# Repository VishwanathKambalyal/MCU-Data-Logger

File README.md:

# 📌 MCU Data Logger

## 📖 Overview

MCU Data Logger is a **hardware-based data logging system** designed to record and store data efficiently. The system is built using the **ATmega328P-AU microcontroller**, **24LC1025 EEPROM**, and **DS1337 RTC** for precise timekeeping. The hardware is designed in **KiCad 9**, with **2-layer PCB**.

### 🔹 Key Components

- **🖥️ ATmega328P-AU (MCU)**
  - Serves as the main processing unit.
  - Handles data acquisition, processing, and communication.
  - Supports multiple communication protocols (UART, SPI, I2C).

- **💾 24LC1025 EEPROM (I2C Storage)**
  - Provides non-volatile memory for data storage.
  - Communicates via the I2C protocol.
  - Can store up to **1 Mbit** of data.

- **⏳ DS1337 Real-Time Clock (RTC)**
  - Maintains accurate timestamps for logged data.
  - Operates using the I2C protocol.
  - Supports alarms and timekeeping even in power-off conditions.

- **🔌 Power System**
  - Operates on a **5V** power supply.
  - Includes **ground (GND) connections** for circuit stability.

- **📡 Communication Interfaces**
  - **UART (Tx, Rx)** for serial communication.
  - **SPI (SCK, MOSI, MISO, RESET)** for high-speed data transfer.
  - **I2C (SDA, SCL)** for sensor and memory communication.

- **🖲️ General-Purpose Input/Output (GPIO)**
  - Available on **D2-D8** pins.
  - Can be used for external sensors or control signals.

---

## 🔧 Features

- ✅ **Microcontroller**: ATmega328P-AU
- ✅ **Memory Storage**: 24LC1025 EEPROM (I2C)
- ✅ **Real-Time Clock (RTC)**: DS1337 (I2C)
- ✅ **Interfaces**:
  - **UART**: Tx, Rx
  - **SPI**: SCK, MOSI, MISO, RESET
  - **I2C**: SDA, SCL
- ✅ **Power Supply**: 5V
- ✅ **GPIOs**: D2-D8 for peripheral connections

---

## 📷 Project Images

### 🔹 Schematic Diagram

### 🔹 PCB Designs

### 🔹 3D PCB Views

| Top View                             | Bottom View                          |
| ------------------------------------ | ------------------------------------ |
|        |   |

---

## 🔌 How to Use

### 1️⃣ Clone the Repository
```bash
git clone https://github.com/VishwanathKambalyal/MCU-Data-Logger.git
```
### 2️⃣ Open Hardware Files in KiCad 9
Navigate to the Hardware folder.
Open the schematic (.sch) and PCB (.kicad_pcb) files.

### 3️⃣ Customize & Manufacture
Modify the PCB design if required.
Generate Gerber files for PCB fabrication.

## 📜 License
This project is licensed under the MIT License – you are free to use, modify, and distribute it as needed.

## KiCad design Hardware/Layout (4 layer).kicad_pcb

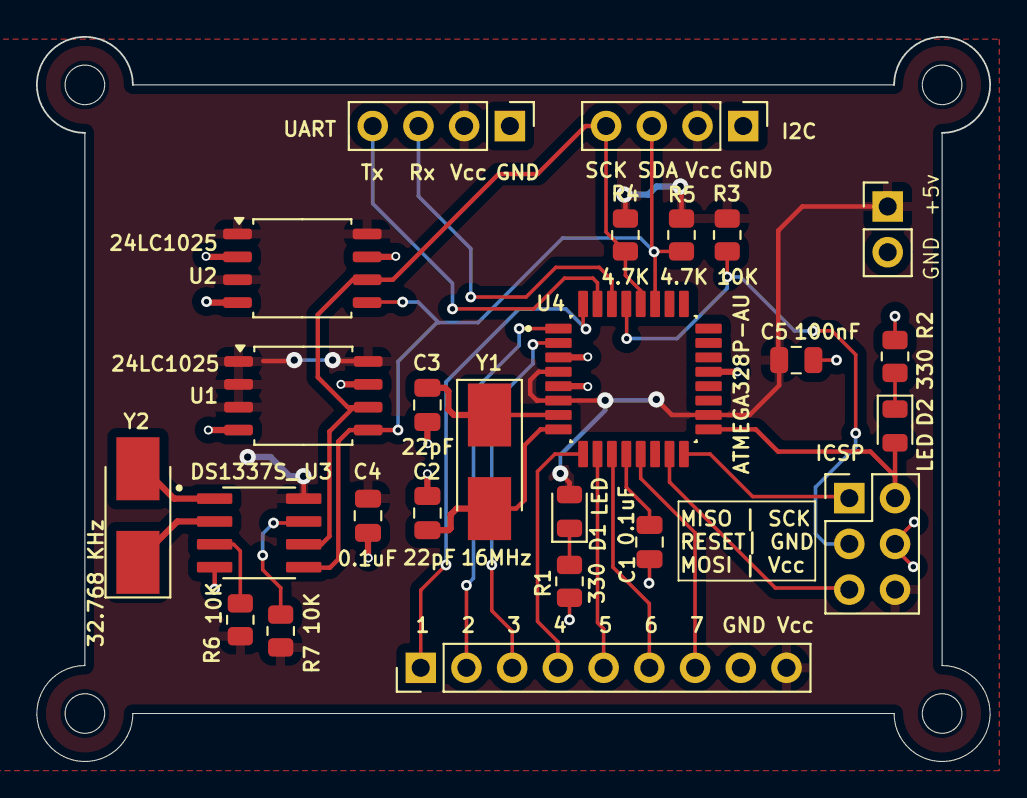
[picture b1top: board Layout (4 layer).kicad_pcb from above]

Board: 2 copper layers, 53.0 x 40.2 mm, 29 parts (0 on the bottom side), 26 nets.

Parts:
BT1: Battery_Cell; PinHeader_1x02_P2.54mm_Vertical
C1, C4: 0.1uF; C_0805_2012Metric
C2, C3: 22pF; C_0805_2012Metric
C5: 100nF; C_0805_2012Metric
D1, D2: LED; LED_0805_2012Metric
H1, H2, H3, H4: MountingHole; MountingHole_2.2mm_M2
J1, J2: Conn_01x04_Pin; PinHeader_1x04_P2.54mm_Vertical
J3: Conn_01x09_Pin; PinHeader_1x09_P2.54mm_Vertical
J4: Conn_02x03_Counter_Clockwise; PinHeader_2x03_P2.54mm_Vertical
R1, R2: 330; R_0805_2012Metric
R3, R6, R7: 10K; R_0805_2012Metric
R4, R5: 4.7K; R_0805_2012Metric
U1, U2: 24LC1025; SOIC-8_5.23x5.23mm_P1.27mm
U3: DS1337S_; SOIC127P600X175-8N
U4: ATMEGA328P-AU; QFP80P900X900X120-32N
Y1: 16MHz; Crystal_SMD_5032-2Pin_5.0x3.2mm_HandSoldering
Y2: 32.768 KHz; Crystal_SMD_5032-2Pin_5.0x3.2mm_HandSoldering

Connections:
/D2: J3.1, U4.32 (PD2)
/D3: J3.2, U4.1 (PD3)
/D4: J3.3, U4.2 (PD4)
/D5: J3.4, U4.9 (PD5)
/D6: J3.5, U4.10 (PD6)
/D7: J3.6, U4.11 (PD7)
/D8: J3.7, U4.13 (PB1)
/MISO: J4.1, U4.16 (PB4)
/MOSI: J4.5, U4.15 (PB3)
/RESET: J4.3, R3.2, U4.29 (PC6/~RESET)
/RX: J2.3, U4.30 (PD0)
/SCK: D2.2 (A), J4.2, U4.17 (PB5)
/SCL: J1.4, R4.2, U1.6 (SCL), U2.6 (SCL), U3.6 (SCL), U4.28 (PC5)
/SDA: J1.3, R5.2, U1.5 (SDA), U2.5 (SDA), U3.5 (SDA), U4.27 (PC4)
/TX: J2.4, U4.31 (PD1)
/Vcc: BT1.1 (+), C4.1, C5.1, D1.2 (A), J1.2, J2.2, J3.9, J4.6, R3.1, R4.1, R5.1, R6.1, R7.1, U1.1 (A0), U1.2 (A1), U1.3 (A2), U1.8 (VCC), U2.1 (A0), U2.3 (A2), U2.8 (VCC), U3.8 (VCC), U4.4 (VCC), U4.6 (VCC), U4.18 (AVCC)
GND: BT1.2 (-), C1.1, C2.1, C3.1, C4.2, C5.2, J1.1, J2.1, J3.8, J4.4, R1.2, R2.1, U1.4 (GND), U1.7 (WP), U2.2 (A1), U2.4 (GND), U2.7 (WP), U3.4 (GND), U4.3 (GND), U4.5 (GND), U4.21 (GND)
unnamed: D1.1 (K), R1.1
unnamed: D2.1 (K), R2.2
unnamed: R7.2, U3.7 (SQW/~INT)
unnamed: U3.1 (X1), Y2.2
unnamed: U3.2 (X2), Y2.1
unnamed: R6.2, U3.3 (~INTA)
unnamed: C1.2, U4.12 (PB0)
unnamed: C3.2, U4.7 (PB6), Y1.1
unnamed: C2.2, U4.8 (PB7), Y1.2

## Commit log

2025-03-12 first commit of this repository
2025-03-12 Added Images
2025-03-20 Added PCB Images.
2025-03-27 Rename images/Screenshot 2025-03-27 191841.png to 2_Layer_PCB.png
